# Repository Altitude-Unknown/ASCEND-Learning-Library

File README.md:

# ASCEND website

A public educational resource library for student teams at two-year community
colleges and four-year universities, their faculty mentors, and university pod
leads. The library is a working
prototype built with **Eleventy, Markdown, Nunjucks templates, and Pagefind**.
The library pages are ordinary static HTML/CSS/JavaScript with no tracking, CMS,
or client-side application framework.

Signed-in features run separately. Members sign in through Clerk
(`clerk.ascendflight.org`) to request membership and upload team data in the
member workspace. It uses the Data API Worker (`api.ascendflight.org`, in `data-api/`), backed by
PostgreSQL/PostGIS and a private R2 bucket. The library itself needs no account.

Production is live at **https://ascendflight.org** (see [Deployment](docs/DEPLOYMENT.md)).

## Preview locally

Use Node.js 22 or newer (Node 22 is selected for deployment).

```sh
npm ci
npm run preview
```

Open **http://localhost:8080**. `preview` first builds the search index, then
starts the live-reloading development server using `_preview/`, including local
large-file downloads. Stop it with Ctrl+C. Production builds use `_site/`.

- `npm run dev`: fast live editing; run `npm run build` to refresh search after content changes.
- `npm run build`: produce the complete static website in `_site/`.
- `npm test`: build, index search, and check internal links/anchors/headings.
- `npx playwright install chromium`, then `npm run test:browser`: real browser,
  responsive, keyboard, search, and automated accessibility checks.

Do not open `_site/index.html` as a `file://` URL: root-relative routes and the
search engine need a local HTTP server. For a static preview without watch mode,
run `python3 -m http.server 8080 --directory _site` after building.

## What is included

- Homepage, global navigation and footer, eight major section landing pages.
- About ASCEND, Science & Research Questions, and Teams & Project Structure
  pages connect the learning resources to the project’s purpose.
- All nine FAA Part 107 reference-topic pages, with Airspace fully prototyped.
- 24 resource records, including two supplied books, five Part 107 slide decks,
  a trainer build guide, grouped aircraft design files, and future placeholders.
- Browser-readable PDF copies plus original DOCX/PPTX files for presentations and activities. Textbooks are web chapters only.
- Trainer and fixed-wing research UAS project pages with STL, DXF, and Fusion files.
- An Electronic Designs section with complete PCB kits (Fusion, schematic, board, BOM, Gerbers).
- Web-first resource pages with optional contributor, source, and review metadata.
- Resource browsing by collection, subject, platform, activity, type, and audience.
- Site-wide static full-text search, including metadata filters.
- Responsive layouts, skip link, keyboard menu, visible focus, reduced-motion
  support, caption/transcript fields, and video loading only on request.
- A real 404 page, local assets, deployment headers, and GitHub build checks.

Supplied educational files are now connected. Videos, worksheets, and quizzes
without supplied material remain marked Planned. Originals are preserved;
importing them does not assert a new content license or regulatory review.
See [the import inventory](docs/IMPORTED-MATERIALS.md) for all 50 originals,
eight reading copies, and the remaining public-storage setup.

## Project structure

```text
content/
  _data/topics.json          Navigation, sections, and subsection lists
  _data/site.json            Library name and description
  _data/materials.json       File inventory, checksums, and centralized URLs
  _includes/layouts/        Page, module, section, and resource templates
  _includes/components/     Cards, browsing tools, practice CTA, icons
  index.njk                 Homepage composition
  sections.njk              Generates the eight topic landing pages
  library.njk               Filterable resource library
  search.njk                Full-text search page
  part107/*.md              Editable Part 107 lessons
  resources/*.md            Central resource records and permanent pages
public/
  assets/                   Shared styles, progressive enhancement, favicon
  downloads/imported/       Distribution files within the Pages asset limit
  _headers                  Optional Cloudflare response headers
  robots.txt                Prototype indexing restriction
scripts/check-site.mjs       Checks built pages and internal links
tests/                     Playwright browser checks
docs/                      Editing, architecture, and deployment instructions
.eleventy.js                Build configuration and content collections
.node-version               Deployment Node version
package-lock.json           Reproducible dependencies; commit this file
ASCEND-Materials/           Local intake originals; ignored by Git
artifacts/                  Local PDF conversion outputs; ignored by Git
_preview/                   Generated local preview including large files
_site/                      Generated deployment output; do not edit or commit
```

## Edit content without editing HTML

Start with [the contributor-to-curator workflow](docs/CONTENT-WORKFLOW.md), then
[the editing guide](docs/EDITING.md). Contributors can send ordinary files;
Markdown is our publishing format. Copy an existing Markdown file,
edit the short metadata block at the top, then write normal Markdown below it.
The site supplies the header, navigation, layout, metadata, and resource cards.

The `permalink` and resource `id` are stable identifiers. Change a file URL in
**one resource record**, not in every lesson. Lessons refer to resource IDs;
resource cards link to the permanent landing page.

## Publishing

See [deployment instructions](docs/DEPLOYMENT.md). The GitHub repository
`Altitude-Unknown/ASCEND-Learning-Library` is connected to Cloudflare Pages
(`ascend-learning-library.pages.dev`, custom domain `ascendflight.org`) with:

| Setting | Value |
| --- | --- |
| Production branch | `main` |
| Build command | `npm run build` |
| Build output | `_site` |
| Root directory | Repository root |
| Node | `22` (also `.node-version`) |

A push to `main` triggers the Cloudflare build and production deployment. No
token belongs in this repository. The Workers deploy separately with Wrangler; see
[operations](docs/data-explorer/OPERATIONS.md) and [the sign-in proxy](docs/data-explorer/AUTH-PROXY.md).

## Before public launch

Complete remaining placeholder content, configure the large-file URLs, verify
accessibility of actual documents and videos,
set a project accessibility/contact channel, confirm the required award
acknowledgment and content licenses, and review the actual Part 107 content.
Then set `prototype: false` in `content/_data/site.json` and change `public/robots.txt` to allow indexing.
The robots file is not access control; a preview URL can still be visited.

Automated accessibility checks support the WCAG 2.2 AA design goal but do not
prove conformance. Include manual keyboard, screen-reader, zoom/reflow, touch,
Windows/browser, and downloadable-document checks before launch.

The prototype's source and sample records do not establish a redistribution
license for future educational materials. Select a repository license and
per-resource content licenses with the project owner before distribution.

## Maintenance

Keep the lockfile in Git. Run the build and browser checks after dependency or
layout updates. Review external URLs and learning content regularly, especially
regulatory material. Search updates with each production build. Large files
belong in object storage, not an ever-growing Git history. An export of `_site/`
can run on another static host without Eleventy, Node, or Cloudflare services.

## Part 107 practice tests

The supplied practice app is integrated at `/part107/practice-tests/`. See
[the review and maintenance notes](docs/PRACTICE-TEST-REVIEW.md) for corrections,
held questions, source CSVs, figure checks, and regeneration instructions.

## ASCEND Data Explorer

`/data/` adds a labeled synthetic demonstration, MapLibre trajectories, filters,
point inspection, time series, altitude profiles and CSV/GeoJSON export.
`/data/upload/` previews and validates CSV locally; administrator import requires
a configured Worker, Hyperdrive, private R2 bucket and PostgreSQL/PostGIS.

- [Architecture and V1 design](docs/DATA_EXPLORER_ARCHITECTURE.md)
- [Setup, deployment, secrets and recovery](docs/data-explorer/OPERATIONS.md)
- [Data standard](docs/ASCEND_DATA_STANDARD.md)
- [API](docs/data-explorer/API.md) and [schema](docs/data-explorer/SCHEMA.md)

No new Cloudflare resources or scientific database are assumed to exist. Leave
`ASCEND_DATA_API_BASE` unset for the synthetic demo; set it only to your deployed
API's actual origin. Build browser bundles with `npm run build:data` after changing
`src/data/`; the normal build and preview commands include this step.

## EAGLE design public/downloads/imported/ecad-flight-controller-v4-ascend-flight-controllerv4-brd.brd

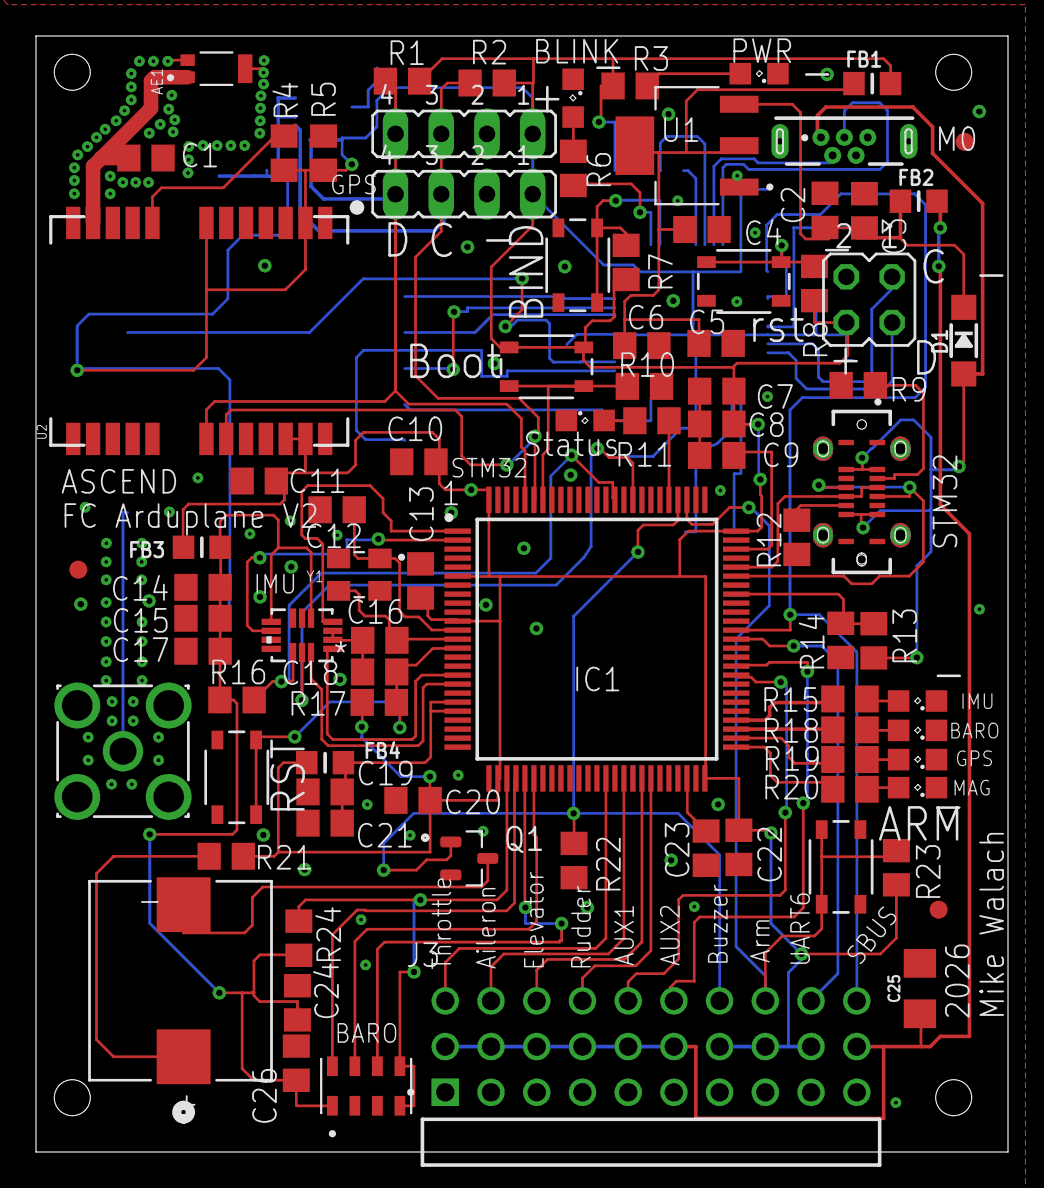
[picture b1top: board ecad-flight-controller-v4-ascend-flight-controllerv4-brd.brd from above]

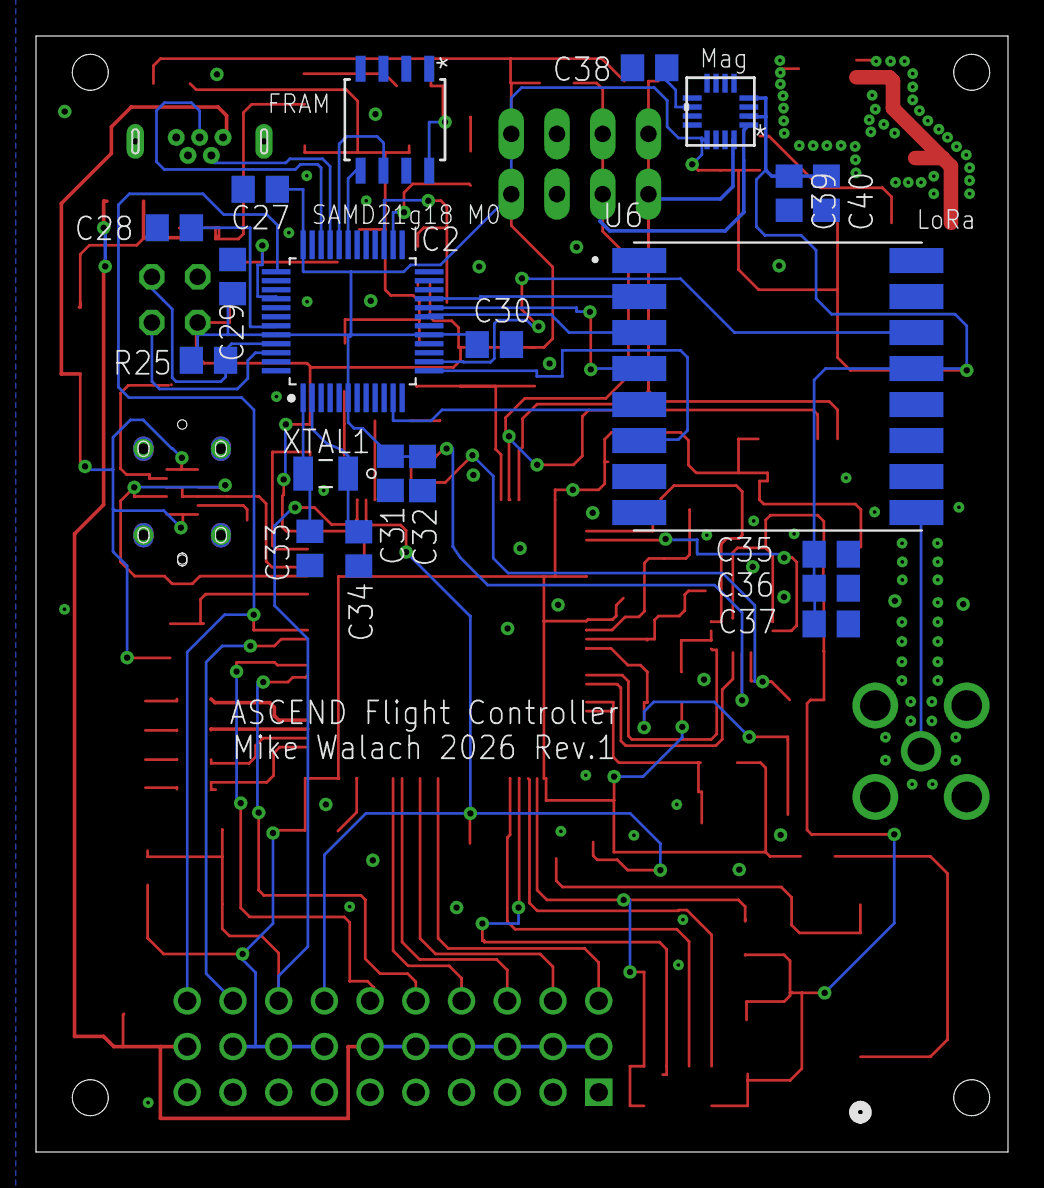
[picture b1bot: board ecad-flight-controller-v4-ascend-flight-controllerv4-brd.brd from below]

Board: 2 copper layers, 54.0 x 62.0 mm, 106 parts (20 on the bottom side), 77 nets.

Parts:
A1: MS561101BA03-50; XDCR_MS561101BA03-50
AE1: W3011; XDCR_W3011
BLINK: SML0805
C1: 2.2pF; C0805
C2, C6, C35, C38: 10uF; C0805
C3, C8, C10, C13, C14, C17, C18, C19, C20, C22, C26, C39, C40: 100nF; C0805
C4, C11, C27, C29, C30, C32, C36: 0.1uF; C0805
C5, C15, C21, C24, C28, C31, C37: 1uF; C0805
C7: 4.7uF; C0805
C9, C23: 2.2uF; C0805
C12, C16: 18pF; C0805
C25: 220uF; 1206
C33, C34: 22pF; C0805
D1: MICROBUILDER_SOD-123
FB1, FB2, FB3, FB4: RC-MASTER-SMD_L0805MP
FID1, FID2, FID3: FIDUCIAL""; FIDUCIAL_1MM
IC1: STM32H743VIT6; QFP50P1600X1600X160-100N
IC2: ATSAMD21G; QFP50P900X900X120-48
J1: 614105150721
J2: USB4120-03-C_REVA6; GCT_USB4120-03-C_REVA6
J3: TSW-110-08-G-T-RA; SAMTEC_TSW-110-08-G-T-RA
JP1, JP2: JUMPER_1_JP4
JP3: JP2Q
LED4, LED5, LED6, LED7: SML0805
LS1: SMTB-0927-TW-RSMTB-0927-TW-R_PUI; SMTB-0927-TW-R_PUI
PWR: SML0805
Q1: 2N7002K-7; SOT91P240X110-3N
R1, R2, R10, R14, R16, R17, R24: 10k; R0805
R3, R6, R11, R15, R18, R19, R20: 2.2K; R0805
R4, R7, R8, R23, R25: 1K; R0805
R5: 100K; R0805
R9, R12: 5.1K; R0805
R13: 4.7k; R0805
R21: 0-100; R0805
R22: 100k; R0805
STATUS: SML0805
SW1, SW2, SW3, SW4, SW5: PTS810SJG250SMTRLFSPTS810; PTS810
U1: TLV1117LV33DCYR; VREG_TLV1117LV33DCYR
U2: GPS_U-BLOX_NEO-M9N; GPS_NEO-M9N
U3: LSM6DSO32TRLGA-14L_2P5X3X0P83_STM; LGA-14L_2P5X3X0P83_STM
U4: 132134132134_AMP; 132134_AMP
U5: MB85RC256VPNF-G-JNERE1FPT-8P-M02_FUJ; FPT-8P-M02_FUJ
U6: RFM95W-915S2; XCVR_RFM95W-915S2
U7: MMC5983MAMMC5983MA_MEM; MMC5983MA_MEM
XTAL1: 32.768kHz; XTAL_ABS07-32.768KHZ-T
Y1: ECS-80-12-33-JGN-TR3; XTAL_ECS-240-8-33-AGN-TR

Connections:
5V-SERVO-RAIL: C25.1, FB2.1, J3.02, J3.05, J3.08, J3.11, J3.14, J3.17, J3.29
+3V3: C7.1, C8.1, C10.1, C11.1, C13.1, C20.1, C22.1, C27.1, C29.1, C30.1, C31.1, C32.1, C35.1, C36.1, C37.1, C39.1, C40.1, FB1.2, FB3.2, FB4.1, IC1.6, IC1.11, IC1.27, IC1.50, IC1.75, IC1.100, IC2.6, IC2.17, IC2.36, IC2.44, J3.20, J3.23, J3.26, JP1.1, JP2.1, JP3.4, R1.1, R2.1, R3.1, R4.2, R5.2, R7.2, R8.2, R17.1, R21.1, R23.2, R25.1, SW3.3, SW3.4, U2.2, U2.7, U2.22, U2.23, U5.8, U6.13, U7.2, U7.4, U7.13
AILERON: IC1.41, J3.06
ARMING_BUTTON: IC1.78, J3.24, R23.1, SW5.1, SW5.2
AUX1: IC1.59, J3.15
AUX2: IC1.60, J3.18
BARO_CS: A1.4, A1.5, IC1.28, R24.2
BIND: IC2.27, R7.1, SW1.1, SW1.2
BLINK: IC1.80, R11.1
BOOT0: IC1.94, R10.1, SW3.1, SW3.2
BUZZER: IC1.79, J3.21, Q1.1, R22.1
D13: IC2.26, R6.1
D+: IC2.34, J1.3
D-: IC2.33, J1.2
DIO0: IC2.14, U6.14
ELEVATOR: IC1.43, J3.09
FILTERED-3.3V: A1.1, C14.1, C15.1, C17.1, C24.1, C26.1, FB3.1, R16.1, R24.1, U3.5, U3.8
GND: A1.2, A1.3, AE1.2, AE1.3, BLINK.C, C1.2, C2.2, C3.2, C4.2, C5.2, C6.2, C7.2, C8.2, C9.2, C10.2, C11.2, C12.2, C13.2, C14.2, C15.2, C16.2, C17.2, C18.2, C19.2, C20.2, C21.2, C22.2, C23.2, C24.2, C25.2, C26.2, C27.2, C28.2, C29.2, C30.2, C31.2, C32.2, C33.2, C34.2, C35.2, C36.2, C37.2, C38.2, C39.2, C40.2, IC1.10, IC1.19, IC1.26, IC1.49, IC1.74, IC1.99, IC2.5, IC2.18, IC2.35, IC2.42, J1.5, J1.S1, J1.S2, J2.A1, J2.A12, J2.B1, J2.B12, J2.S1, J2.S2, J2.S3, J2.S4, J3.01, J3.04, J3.07, J3.10, J3.13, J3.16, J3.19, J3.22, J3.25, J3.28, JP1.2, JP2.2, JP3.3, LED4.C, LED5.C, LED6.C, LED7.C, PWR.C, Q1.2, R5.1, R9.2, R10.2, R12.2, R14.2, R22.2, STATUS.C, SW1.3, SW1.4, SW2.3, SW2.4, SW4.3, SW4.4, SW5.3, SW5.4, U1.1, U2.10, U2.12, U2.13, U2.24, U3.2, U3.3, U3.6, U3.7, U4.2, U4.3, U4.4, U4.5, U5.4, U6.1, U6.8, U6.10, U7.5, U7.9, U7.11, Y1.2, Y1.4
GPS-HEALTH: IC1.52, R19.1
GPS_ANT1: AE1.1, C1.1, U2.11
GYRO_CS: IC1.86, R16.2, U3.12
I2C1_SCL: IC1.95, JP1.3, JP2.3, R2.2, U2.19, U7.1
I2C1_SDA: IC1.96, JP1.4, JP2.4, R1.2, U2.18, U7.16
IMU-HEALTH: IC1.54, R15.1
IMU_INT1: IC1.1, U3.4
IMU_INT2: IC1.2, U3.9
LORA_ANT: U4.1, U6.9
LORA_RESET: IC2.13, U6.6
MAGNATOMETER-HEALTH: IC1.51, R20.1
MISO: IC2.21, U6.2
MOSI: IC2.19, U6.3
unnamed: C9.1, IC1.73
unnamed: C23.1, IC1.48
unnamed: C19.1, C21.1, FB4.2, IC1.20, IC1.21
unnamed: R4.1, U2.8
unnamed: LS1.1, R21.2
unnamed: LS1.2, Q1.3
unnamed: LED4.A, R15.2
unnamed: R11.2, STATUS.A
unnamed: C4.1, C5.1, C6.1, FB1.1, U1.2, U1.4
unnamed: C2.1, C3.1, D1.C, FB2.2, U1.3
unnamed: LED5.A, R18.2
unnamed: C28.1, IC2.43
unnamed: LED6.A, R19.2
unnamed: LED7.A, R20.2
unnamed: C34.1, IC2.2, XTAL1.1
unnamed: C33.1, IC2.1, XTAL1.2
unnamed: BLINK.A, R6.2
unnamed: C38.1, U7.10
unnamed: PWR.A, R3.2
unnamed: J2.A5, R9.1
unnamed: J2.B5, R12.1
NRST: C18.1, IC1.14, R17.2, SW4.1, SW4.2
NSS: IC2.11, U6.5
OSC-IN: C12.1, IC1.12, Y1.1
OSC-OUT: C16.1, IC1.13, Y1.3
PRESSURE-HEALTH: IC1.53, R18.1
RCIN_SBUS: IC1.64, IC2.37, J3.30
RESET: IC2.40, R8.1, SW2.1, SW2.2
RUDDER: IC1.44, J3.12
SCK: IC2.20, U6.4
SCL: IC2.32, U5.6
SDA: IC2.31, U5.5
SPI1_MISO: A1.6, IC1.30
SPI1_MOSI: A1.7, IC1.31
SPI1_SCK: A1.8, IC1.29
SPI2_MISO: IC1.17, U3.1
SPI2_MOSI: IC1.18, U3.14
SPI2_SCK: IC1.84, U3.13
SWCLK: IC2.45, JP3.1, R25.2
SWDIO: IC2.46, JP3.2
THROTTLE: IC1.39, J3.03
USART6_TX: IC1.63, J3.27
USB_5V: D1.A, J1.1, J2.A4, J2.A9, J2.B4, J2.B9, R13.1
USB_D+: IC1.71, J2.A6, J2.B6
USB_D−: IC1.70, J2.A7, J2.B7
USB_VBUS_SENSE: IC1.68, R13.2, R14.1

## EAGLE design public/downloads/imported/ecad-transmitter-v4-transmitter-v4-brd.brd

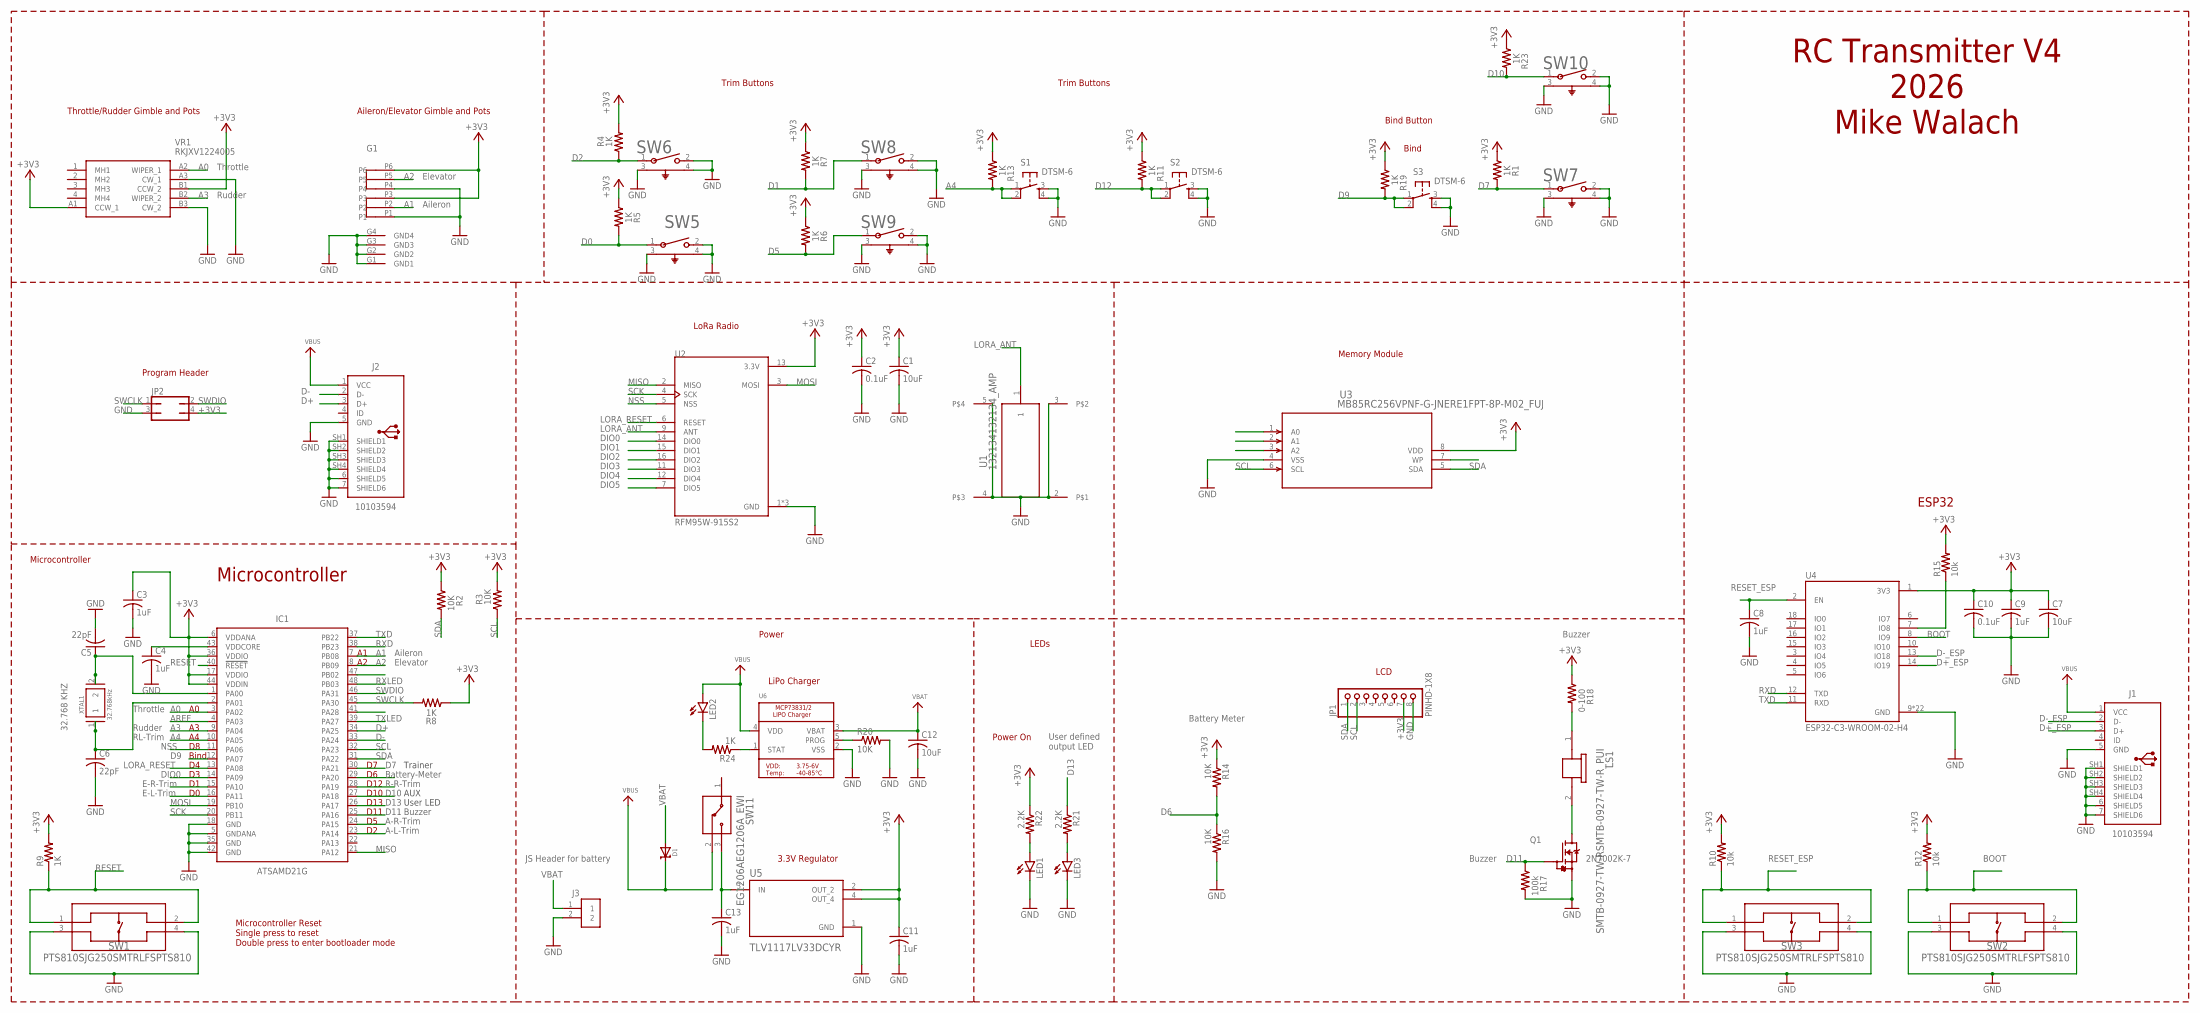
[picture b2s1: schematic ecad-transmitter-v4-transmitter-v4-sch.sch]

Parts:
C1, C7, C12: 10uF; C0805
C2, C10: 0.1uF; C0805
C3, C4, C8, C9, C11, C13: 1uF; C0805
C5, C6: 22pF; C0805
D1: MICROBUILDER_DIODE-SCHOTTKYSOD-123; MICROBUILDER_SOD-123
G1: C37323742
IC1: ATSAMD21G; QFP50P900X900X120-48
J1, J2: 10103594
J3: S2B-PH-K-S(LF)(SN)
JP1: PINHD-1X8; 1X08
JP2: JP2Q
LED1, LED2, LED3: LEDSML0805; SML0805
LS1: SMTB-0927-TW-RSMTB-0927-TW-R_PUI; SMTB-0927-TW-R_PUI
Q1: 2N7002K-7; SOT91P240X110-3N
R1, R4, R5, R6, R7, R8, R9, R11, R13, R19, R23, R24: 1K; R0805
R2, R3, R14, R16, R20: 10K; R0805
R10, R12, R15: 10k; R0805
R17: 100k; R0805
R18: 0-100; R0805
R21, R22: 2.2K; R0805
S1, S2, S3: DTSM-6
SW1, SW2, SW3: PTS810SJG250SMTRLFSPTS810; PTS810
SW5, SW6, SW7, SW8, SW9, SW10: 1825027-8SW2_1825027-C_TEC; SW2_1825027-C_TEC
SW11: EG1206AEG1206A_EWI; EG1206A_EWI
U1: 132134132134_AMP; 132134_AMP
U2: RFM95W-915S2; XCVR_RFM95W-915S2
U3: MB85RC256VPNF-G-JNERE1FPT-8P-M02_FUJ; FPT-8P-M02_FUJ
U4: ESP32-C3-WROOM-02-H4; MODULE_ESP32-C3-WROOM-02-H4
U5: TLV1117LV33DCYR; VREG_TLV1117LV33DCYR
U6: MICROBUILDER_MCP73831/2; MICROBUILDER_SOT23-5
VR1: RKJXV1224005
XTAL1: 32.768kHz; XTAL_ABS07-32.768KHZ-T

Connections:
+3V3: C1.1, C2.1, C3.1, C7.1, C9.1, C10.1, C11.1, G1.P3, G1.P6, IC1.6 (VDDANA), IC1.17 (VDDIO), IC1.36 (VDDIO), IC1.44 (VDDIN), JP1.7, JP2.4, R1.1, R2.1, R3.2, R4.2, R5.1, R6.1, R7.1, R8.1, R9.2, R10.2, R11.1, R12.2, R13.1, R14.1, R15.2, R18.1, R19.1, R22.1, R23.1, U2.13 (3.3V), U3.8 (VDD), U4.1 (3V3), U5.2 (OUT_2), U5.4 (OUT_4), VR1.A1 (CCW_1), VR1.B1 (CCW_2)
A0: IC1.3 (PA02), VR1.A2 (WIPER_1)
A1: G1.P2, IC1.7 (PB08)
A2: G1.P5, IC1.8 (PB09)
A3: IC1.9 (PA04), VR1.B2 (WIPER_2)
A4: IC1.10 (PA05), R13.2, S1.1, S1.2
AREF: IC1.4 (PA03)
BOOT: R12.1, SW2.1, SW2.2, U4.8 (IO9)
D0: IC1.16 (PA11), R5.2, SW5.1
D1: IC1.15 (PA10), R7.2, SW8.1
D2: IC1.23 (PA14), R4.1, SW6.1
D5: IC1.24 (PA15), R6.2, SW9.1
D6: IC1.29 (PA20), R14.2, R16.1
D7: IC1.30 (PA21), R1.2, SW7.1
D9: IC1.12 (PA07), R19.2, S3.1, S3.2
D10: IC1.27 (PA18), R23.2, SW10.1
D11: IC1.25 (PA16), Q1.1 (G), R17.1
D12: IC1.28 (PA19), R11.2, S2.1, S2.2
D13: IC1.26 (PA17), R21.1
D+: IC1.34 (PA25), J2.3 (D+)
D+_ESP: J1.3 (D+), U4.14 (IO19)
D-: IC1.33 (PA24), J2.2 (D-)
D-_ESP: J1.2 (D-), U4.13 (IO18)
DIO0: IC1.14 (PA09), U2.14 (DIO0)
DIO1: U2.15 (DIO1)
DIO2: U2.16 (DIO2)
DIO3: U2.11 (DIO3)
DIO4: U2.12 (DIO4)
DIO5: U2.7 (DIO5)
GND: C1.2, C2.2, C3.2, C4.2, C5.2, C6.2, C7.2, C8.2, C9.2, C10.2, C11.2, C12.2, C13.2, G1.G1 (GND1), G1.G2 (GND2), G1.G3 (GND3), G1.G4 (GND4), G1.P1, G1.P4, IC1.5 (GNDANA), IC1.18 (GND), IC1.35 (GND), IC1.42 (GND), J1.5 (GND), J1.6 (SHIELD5), J1.7 (SHIELD6), J1.SH1 (SHIELD1), J1.SH2 (SHIELD2), J1.SH3 (SHIELD3), J1.SH4 (SHIELD4), J2.5 (GND), J2.6 (SHIELD5), J2.7 (SHIELD6), J2.SH1 (SHIELD1), J2.SH2 (SHIELD2), J2.SH3 (SHIELD3), J2.SH4 (SHIELD4), J3.2, JP1.8, JP2.3, LED1.C, LED3.C, Q1.2 (S), R16.2, R17.2, R20.2, S1.3, S1.4, S2.3, S2.4, S3.3, S3.4, SW1.3, SW1.4, SW2.3, SW2.4, SW3.3, SW3.4, SW5.2, SW5.3, SW5.4, SW6.2, SW6.3, SW6.4, SW7.2, SW7.3, SW7.4, SW8.2, SW8.3, SW8.4, SW9.2, SW9.3, SW9.4, SW10.2, SW10.3, SW10.4, U1.2, U1.3, U1.4, U1.5, U2.1 (GND), U2.8 (GND), U2.10 (GND), U3.4 (VSS), U4.9 (GND), U4.19 (GND), U4.20 (GND), U4.21 (GND), U4.22 (GND), U4.23 (GND), U4.24 (GND), U4.25 (GND), U4.26 (GND), U4.27 (GND), U4.28 (GND), U4.29 (GND), U4.30 (GND), U4.31 (GND), U4.32 (GND), U4.33 (GND), U4.34 (GND), U4.35 (GND), U4.36 (GND), U4.37 (GND), U4.38 (GND), U4.39 (GND), U5.1 (GND), U6.2 (VSS), VR1.A3 (CW_1), VR1.B3 (CW_2)
LORA_ANT: U1.1, U2.9 (ANT)
LORA_RESET: IC1.13 (PA08), U2.6 (RESET)
MISO: IC1.21 (PA12), U2.2 (MISO)
MOSI: IC1.19 (PB10), U2.3 (MOSI)
unnamed: C4.1, IC1.43 (VDDCORE)
unnamed: LS1.1, R18.2
unnamed: R24.1, U6.1 (STAT)
unnamed: LS1.2, Q1.3 (D)
unnamed: LED2.C, R24.2
unnamed: LED3.A, R21.2
unnamed: R20.1, U6.5 (PROG)
unnamed: C6.1, IC1.2 (PA01), XTAL1.1
unnamed: C5.1, IC1.1 (PA00), XTAL1.2
unnamed: C13.1, SW11.3, U5.3 (IN)
unnamed: R15.1, U4.7 (IO8)
unnamed: LED1.A, R22.2
NSS: IC1.11 (PA06), U2.5 (NSS)
RESET: IC1.40 (!RESET), R9.1, SW1.1, SW1.2
RESET_ESP: C8.1, R10.1, SW3.1, SW3.2, U4.2 (EN)
RXD: IC1.38 (PB23), U4.12 (TXD)
RXLED: IC1.48 (PB03)
SCK: IC1.20 (PB11), U2.4 (SCK)
SCL: IC1.32 (PA23), JP1.2, R3.1, U3.6 (SCL)
SDA: IC1.31 (PA22), JP1.1, R2.2, U3.5 (SDA)
SWCLK: IC1.45 (PA30), JP2.1, R8.2
SWDIO: IC1.46 (PA31), JP2.2
TXD: IC1.37 (PB22), U4.11 (RXD)
TXLED: IC1.39 (PA27)
VBAT: C12.1, D1.A, J3.1, U6.3 (VBAT)
VBUS: D1.C, J1.1 (VCC), J2.1 (VCC), LED2.A, SW11.2, U6.4 (VDD)

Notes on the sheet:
Power
Microcontroller
32.768 KHZ
Program Header
D10
LEDs
Power On
3.3V Regulator
Microcontroller Reset Single press to reset Double press to enter bootloader mode
D13
D11
D12
Throttle
Aileron
Elevator
Rudder
Battery-Meter
E-L-Trim
E-R-Trim
A-L-Trim
A-R-Trim
R-R-Trim
LiPo Charger
LCD
RL-Trim
Bind
Buzzer
Throttle/Rudder Gimble and Pots
Aileron/Elevator Gimble and Pots
Trim Buttons
Bind Button
LoRa Radio
Memory Module
Battery Meter
JS Header for battery
User defined output LED
User LED
AUX
Trainer
ESP32

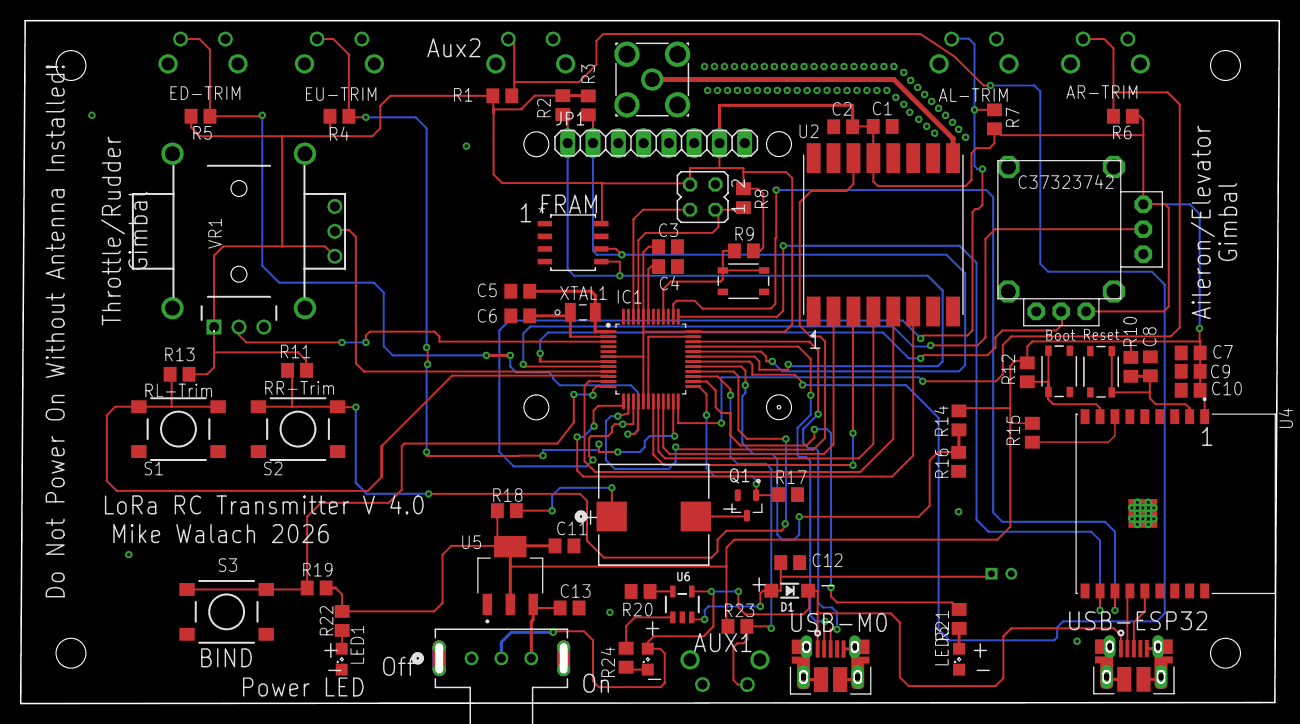
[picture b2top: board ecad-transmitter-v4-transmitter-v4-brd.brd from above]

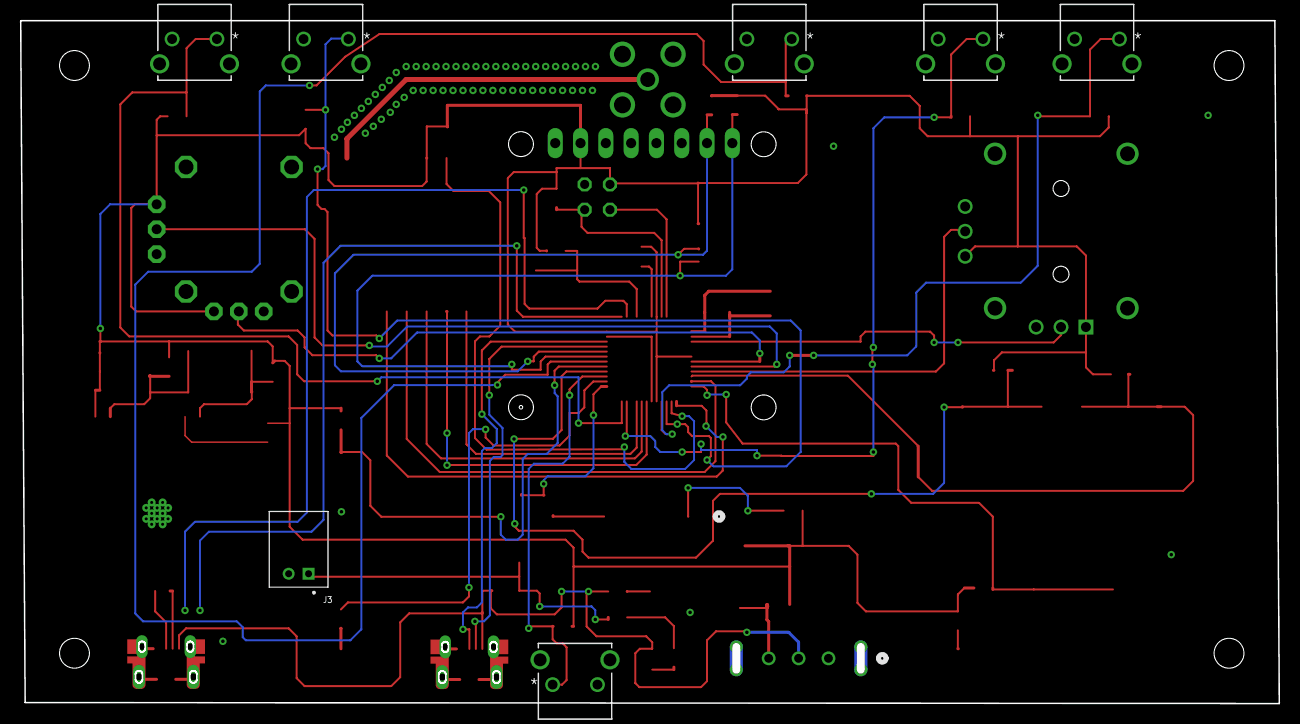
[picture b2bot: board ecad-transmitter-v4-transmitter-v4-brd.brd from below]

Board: 2 copper layers, 126.4 x 68.5 mm, 71 parts (7 on the bottom side), 52 nets.

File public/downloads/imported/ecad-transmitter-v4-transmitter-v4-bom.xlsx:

Reference Designators | Value | Part Number | Part Number | Part Number
C1, C7, C12 | 10uF | 587-1295-1-ND
C2, C10 | 0.1uF | 478-KGM21NR71E104KTTR-ND
C3, C4, C8, C9, C11, C13 | 1uF | 478-5034-1-ND
C5, C6 | 22pF | 478-KGM21BCG2A220JTTR-ND
D1 | Shottky | MBR120LSFT1GOSCT-ND
G1 | Aileron/Elevator Gimbal | C37323742 (Order from JLPCB)
IC1 | ATSAMD21G | ATSAMD21G18A-AU-ND
J1, J2 | Micro-USB | 609-4050-2-ND
J3 | S2B-PH-K-S(LF)(SN) (JST Connector) | 455-1719-ND
JP1 | PINHD-1X8 -Female header for LCD | 732-61300811821-ND
JP2 | Do not Solder -- Program header | N/A
LED1, LED2, LED3 | Red, green, orange | 1497-1170-1-ND | 1497-1216-1-ND | 1497-1188-1-ND
LS1 | SMTB-0927-TW-RSMTB-0927-TW-R_PUI (Speaker) | 668-SMTB-0927-TW-RTR-ND
Q1 | 2N7002K-7 MOSFET | 2N7002K-7DITR-ND
R1, R4, R5, R6, R7, R8, R9, R11, R13, R19, R23, R24 | 1K | YAG1321CT-ND
R2, R3, R14, R16, R20 | 10K | RNCP0805FTD10K0TR-ND
R10, R12, R15 | 10k | RNCP0805FTD10K0TR-ND
R17 | 100k | 541-CRCW0805100KJNEBCT-ND
R18 | 29 or 100 ohm | 738-RMCF0805JT27R0TR-ND | RG20P100BTR-ND
R21, R22 | 2.2K | 497-17720-ND
S1, S2, S3 | DTSM-6 Large pushbuttons | 141-TL3301NF160QG-KRCT-ND
SW1, SW2, SW3 | PTS810SJG250SMTRLFSPTS810 Small pushbuttons | CKN10504TR-ND
SW5, SW6, SW7, SW8, SW9, SW10 | 1825027-8SW2_1825027-C_TEC (90 degree buttons) | 450-1657-ND
SW11 | EG1206AEG1206A_EWI (Slide Switch) | EG1917-ND
U1 | 132134132134_AMP (90 Degree Antenna Jack) | SAM8856-ND
U2 | RFM95W-915S2 LoRa Module | RFM95W-915S2
U3 | MB85RC256VPNF-G-JNERE1FPT-8P-M02_FUJ. (FRAM) | 865-MB85RC256VPNF-G-AMERE2TR-ND
U4 | ESP32-C3-WROOM-02-H4 (ESP-32) | 1965-ESP32-C3-WROOM-02-H4CT-ND
U5 | TLV1117LV33DCYR. (3.3V regulator 1 amp) | 296-21113-2-ND
U6 | LiPo Charge Controller | 10118194-0001LF
VR1 | Throttle/Rudder Gimbal | C37323741 | YF16-DFL7.2-B5Ko(45-10)B5Ko(55)-RG-A22
XTAL1 | 32.768kHz | 535-11898-2-ND

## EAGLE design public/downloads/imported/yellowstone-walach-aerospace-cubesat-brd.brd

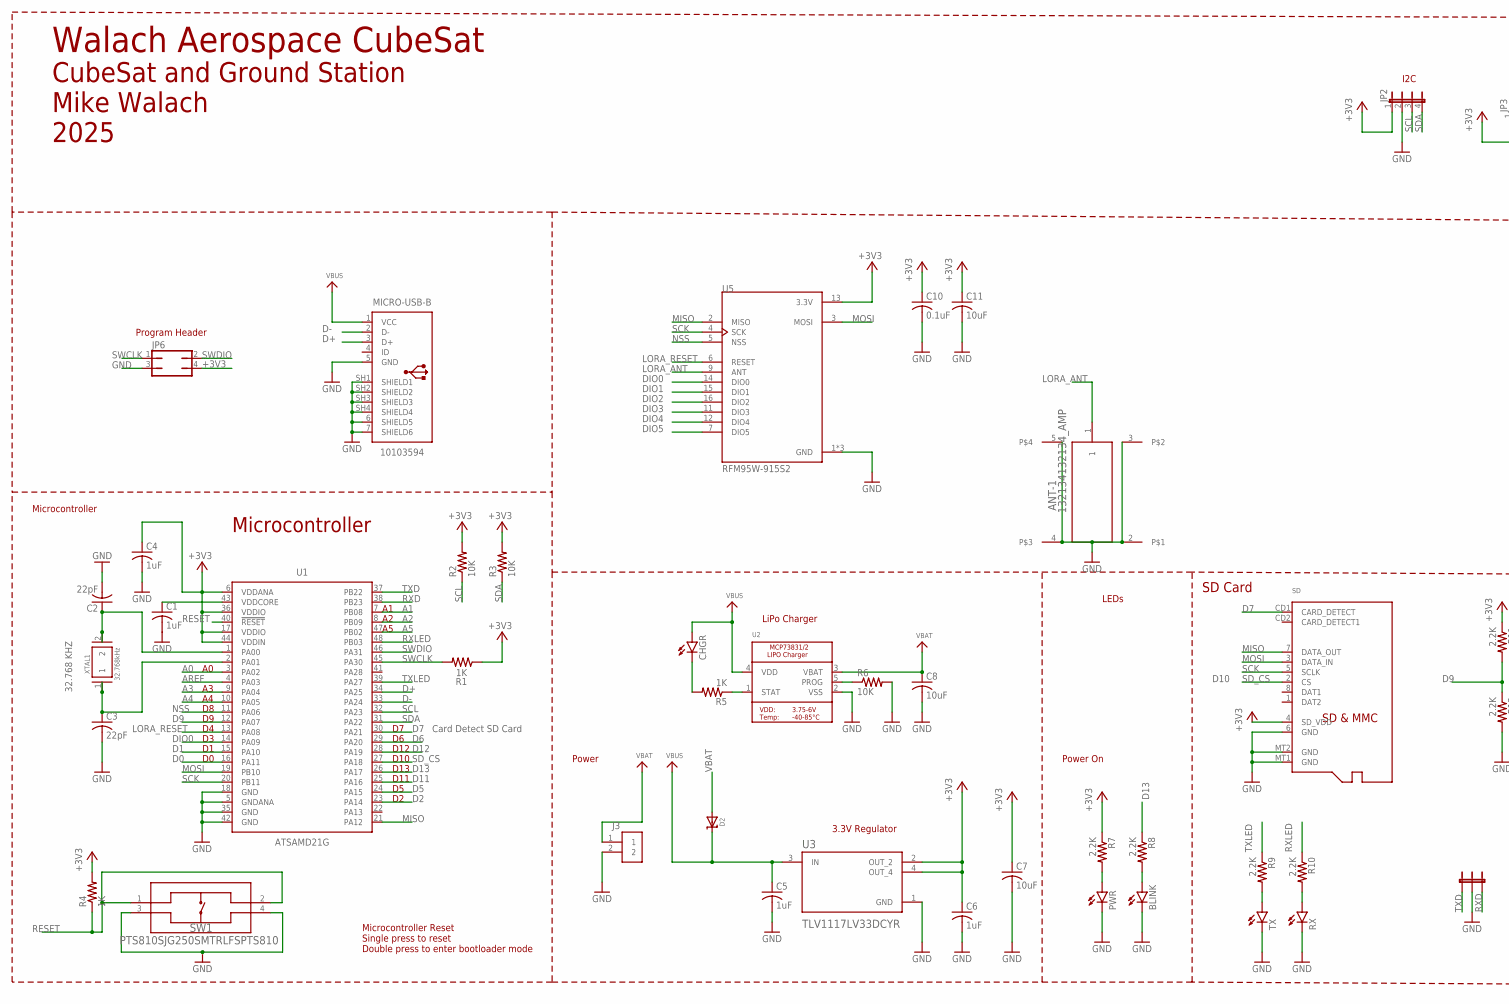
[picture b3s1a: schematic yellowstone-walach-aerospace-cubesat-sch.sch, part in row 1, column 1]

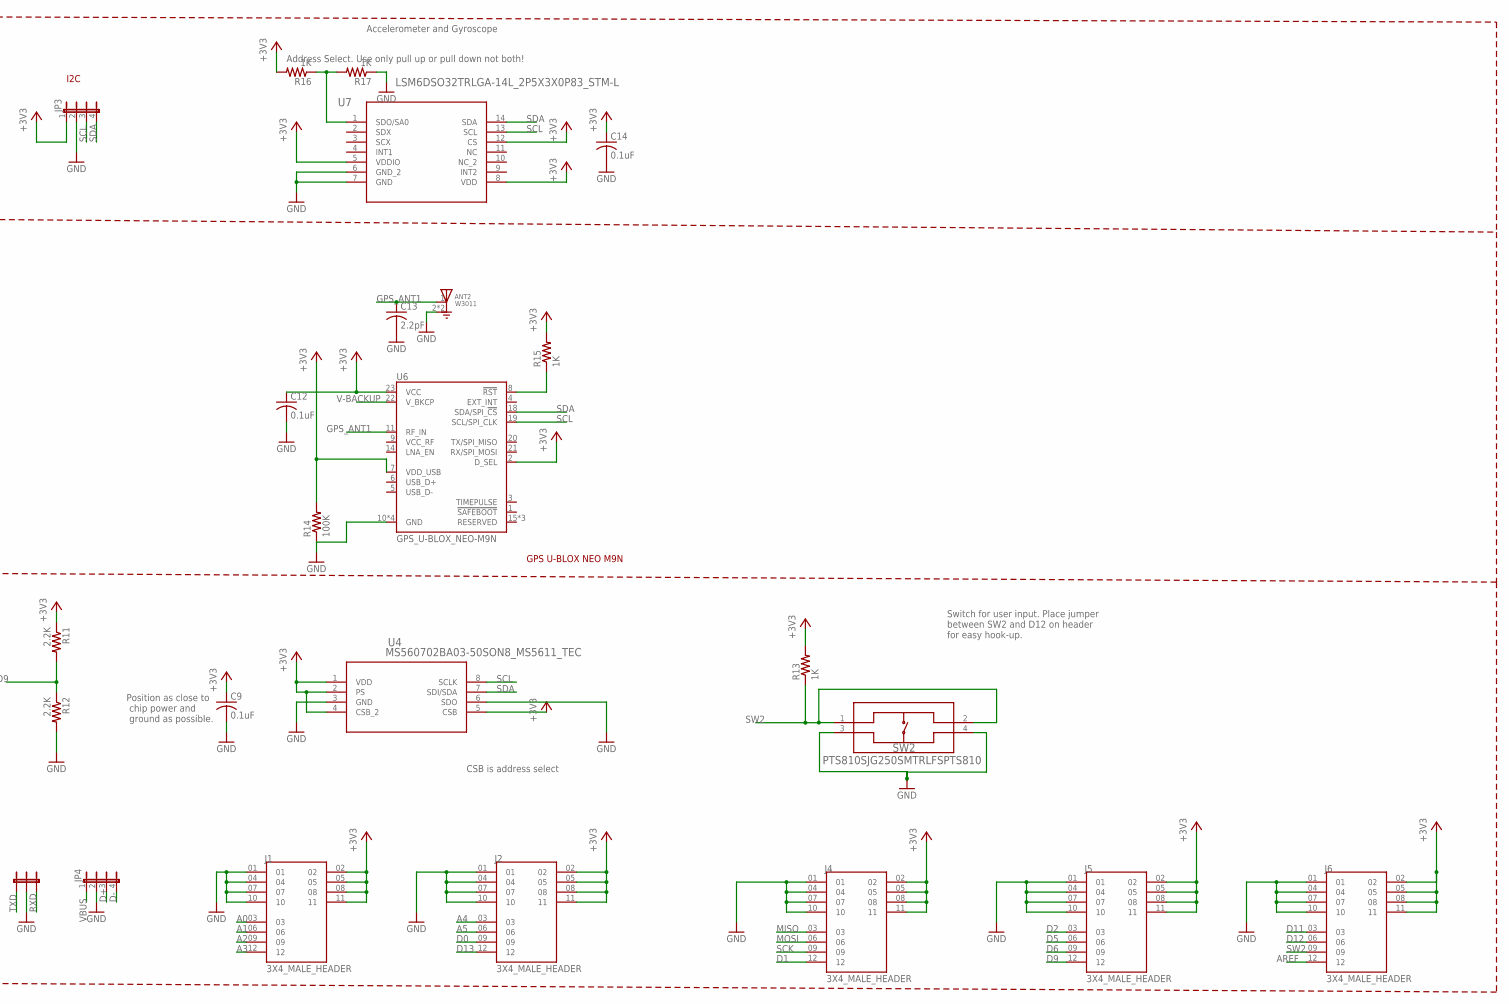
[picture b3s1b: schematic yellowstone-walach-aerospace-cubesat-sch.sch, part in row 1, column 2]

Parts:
ANT2: W3011; XDCR_W3011
ANT-1: 132134132134_AMP; 132134_AMP
BLINK: LEDSML0805; SML0805
C1, C4, C5, C6: 1uF; C0805
C2, C3: 22pF; C0805
C7, C8, C11: 10uF; C0805
C9, C10, C12, C14: 0.1uF; C0805
C13: 2.2pF; C0805
CHGR: LEDSML0805; SML0805
D2: MICROBUILDER_DIODE-SCHOTTKYSOD-123; MICROBUILDER_SOD-123
J1, J2, J4, J5, J6: 3X4_MALE_HEADER; TSW-104-07-F-T_SAMTEC_TSW-104-07-F-T
J3: S2B-PH-K-S(LF)(SN)
JP2, JP3, JP4: JP4E; JP4
JP5: 3-PIN-JUMPER
JP6: JP2Q
MICRO-USB-B: 10103594
PWR: LEDSML0805; SML0805
R1, R4, R5, R13, R15, R16, R17: 1K; R0805
R2, R3, R6: 10K; R0805
R7, R8, R9, R10, R11, R12: 2.2K; R0805
R14: 100K; R0805
RX: LEDSML0805; SML0805
SD: MICROBUILDER_MICROSD
SW1, SW2: PTS810SJG250SMTRLFSPTS810; PTS810
TX: LEDSML0805; SML0805
U1: ATSAMD21G; QFP50P900X900X120-48
U2: MICROBUILDER_MCP73831/2; MICROBUILDER_SOT23-5
U3: TLV1117LV33DCYR; VREG_TLV1117LV33DCYR
U4: MS560702BA03-50SON8_MS5611_TEC; SON8_MS5611_TEC
U5: RFM95W-915S2; XCVR_RFM95W-915S2
U6: GPS_U-BLOX_NEO-M9N; GPS_NEO-M9N
U7: LSM6DSO32TRLGA-14L_2P5X3X0P83_STM-L; LGA-14L_2P5X3X0P83_STM-L
XTAL1: 32.768kHz; XTAL_ABS07-32.768KHZ-T

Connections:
+3V3: C4.1, C6.1, C7.1, C9.1, C10.1, C11.1, C12.1, C14.1, J1.02, J1.05, J1.08, J1.11, J2.02, J2.05, J2.08, J2.11, J4.02, J4.05, J4.08, J4.11, J5.02, J5.05, J5.08, J5.11, J6.02, J6.05, J6.08, J6.11, JP2.1, JP3.1, JP6.4, R1.1, R2.2, R3.2, R4.2, R7.1, R11.1, R13.2, R14.2, R15.2, R16.2, SD.4 (SD_VDD), U1.6 (VDDANA), U1.17 (VDDIO), U1.36 (VDDIO), U1.44 (VDDIN), U3.2 (OUT_2), U3.4 (OUT_4), U4.1 (VDD), U4.2 (PS), U4.4 (CSB_2), U4.5 (CSB), U5.13 (3.3V), U6.2 (D_SEL), U6.7 (VDD_USB), U6.23 (VCC), U7.5 (VDDIO), U7.8 (VDD), U7.12 (CS)
A0: J1.03, U1.3 (PA02)
A1: J1.06, U1.7 (PB08)
A2: J1.09, U1.8 (PB09)
A3: J1.12, U1.9 (PA04)
A4: J2.03, U1.10 (PA05)
A5: J2.06, U1.47 (PB02)
AREF: J6.12, U1.4 (PA03)
D0: J2.09, U1.16 (PA11)
D1: J4.12, U1.15 (PA10)
D2: J5.03, U1.23 (PA14)
D5: J5.06, U1.24 (PA15)
D6: J5.09, U1.29 (PA20)
D7: SD.CD1 (CARD_DETECT), U1.30 (PA21)
D9: J5.12, R11.2, R12.1, U1.12 (PA07)
D11: J6.03, U1.25 (PA16)
D12: J6.06, U1.28 (PA19)
D13: J2.12, R8.1, U1.26 (PA17)
D+: JP4.3, MICRO-USB-B.3 (D+), U1.34 (PA25)
D-: JP4.4, MICRO-USB-B.2 (D-), U1.33 (PA24)
DIO0: U1.14 (PA09), U5.14 (DIO0)
DIO1: U5.15 (DIO1)
DIO2: U5.16 (DIO2)
DIO3: U5.11 (DIO3)
DIO4: U5.12 (DIO4)
DIO5: U5.7 (DIO5)
GND: ANT2.2 (GND), ANT2.3 (GND), ANT-1.2, ANT-1.3, ANT-1.4, ANT-1.5, BLINK.C, C1.2, C2.2, C3.2, C4.2, C5.2, C6.2, C7.2, C8.2, C9.2, C10.2, C11.2, C12.2, C13.2, C14.2, J1.01, J1.04, J1.07, J1.10, J2.01, J2.04, J2.07, J2.10, J3.2, J4.01, J4.04, J4.07, J4.10, J5.01, J5.04, J5.07, J5.10, J6.01, J6.04, J6.07, J6.10, JP2.2, JP3.2, JP4.2, JP5.2, JP6.3, MICRO-USB-B.5 (GND), MICRO-USB-B.6 (SHIELD5), MICRO-USB-B.7 (SHIELD6), MICRO-USB-B.SH1 (SHIELD1), MICRO-USB-B.SH2 (SHIELD2), MICRO-USB-B.SH3 (SHIELD3), MICRO-USB-B.SH4 (SHIELD4), PWR.C, R6.2, R12.2, R14.1, R17.1, RX.C, SD.6 (GND), SD.MT1 (GND), SD.MT2 (GND), SW1.3, SW1.4, SW2.3, SW2.4, TX.C, U1.5 (GNDANA), U1.18 (GND), U1.35 (GND), U1.42 (GND), U2.2 (VSS), U3.1 (GND), U4.3 (GND), U4.6 (SDO), U5.1 (GND), U5.8 (GND), U5.10 (GND), U6.10 (GND), U6.12 (GND), U6.13 (GND), U6.24 (GND), U7.6 (GND_2), U7.7 (GND)
GPS_ANT1: ANT2.1 (FEED), C13.1, U6.11 (RF_IN)
LORA_ANT: ANT-1.1, U5.9 (ANT)
LORA_RESET: U1.13 (PA08), U5.6 (RESET)
MISO: J4.03, SD.7 (DATA_OUT), U1.21 (PA12), U5.2 (MISO)
MOSI: J4.06, SD.3 (DATA_IN), U1.19 (PB10), U5.3 (MOSI)
unnamed: C1.1, U1.43 (VDDCORE)
unnamed: R5.1, U2.1 (STAT)
unnamed: CHGR.C, R5.2
unnamed: R6.1, U2.5 (PROG)
unnamed: BLINK.A, R8.2
unnamed: R9.2, TX.A
unnamed: R10.2, RX.A
unnamed: R15.1, U6.8 (!RST)
unnamed: C3.1, U1.2 (PA01), XTAL1.1
unnamed: R16.1, R17.2, U7.1 (SDO/SA0)
unnamed: C2.1, U1.1 (PA00), XTAL1.2
unnamed: PWR.A, R7.2
NSS: U1.11 (PA06), U5.5 (NSS)
RESET: R4.1, SW1.1, SW1.2, U1.40 (!RESET)
RXD: JP5.3, U1.38 (PB23)
RXLED: R10.1, U1.48 (PB03)
SCK: J4.09, SD.5 (SCLK), U1.20 (PB11), U5.4 (SCK)
SCL: JP2.3, JP3.3, R2.1, U1.32 (PA23), U4.8 (SCLK), U6.19 (SCL/SPI_CLK), U7.13 (SCL)
SDA: JP2.4, JP3.4, R3.1, U1.31 (PA22), U4.7 (SDI/SDA), U6.18 (SDA/SPI_!CS!), U7.14 (SDA)
SD_CS: SD.2 (CS), U1.27 (PA18)
SW2: J6.09, R13.1, SW2.1, SW2.2
SWCLK: JP6.1, R1.2, U1.45 (PA30)
SWDIO: JP6.2, U1.46 (PA31)
TXD: JP5.1, U1.37 (PB22)
TXLED: R9.1, U1.39 (PA27)
V-BACKUP: U6.22 (V_BKCP)
VBAT: C8.1, D2.A, J3.1, U2.3 (VBAT)
VBUS: C5.1, CHGR.A, D2.C, JP4.1, MICRO-USB-B.1 (VCC), U2.4 (VDD), U3.3 (IN)

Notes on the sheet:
Power
SD Card
Microcontroller
32.768 KHZ
CubeSat and Ground Station Mike Walach 2025
LiPo Charger
D10
LEDs
Power On
Microcontroller Reset Single press to reset Double press to enter bootloader mode
Walach Aerospace CubeSat
D13
D11
D12
I2C
Card Detect SD Card
GPS U-BLOX NEO M9N
Address Select. Use only pull up or pull down not both!
Accelerometer and Gyroscope
CSB is address select
Position as close to chip power and ground as possible.
Switch for user input. Place jumper between SW2 and D12 on header for easy hook-up.
Program Header
3.3V Regulator

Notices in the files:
parts and their libraries:
SparkFun-Capacitors: Licensing: Creative Commons ShareAlike 4.0 International - https://creativecommons.org/licenses/by-sa/4.0
COPYRIGHT: Copyright (C) 2024 Ultra Librarian. All rights reserved.
COPYRIGHT: Copyright (C) 2026 Ultra Librarian. All rights reserved.
